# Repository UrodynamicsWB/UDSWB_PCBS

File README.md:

# UDSWB_PCBS

Several PCBs are required in order to manufacture the low-cost urodynamics system. The required file shave been supplied in thi repository.
The system requires one System Controller PCB and two Pressure Sensor PCBs to perform an investigtion.
When manufacturing the system it is best to order 5 System Controller PCBs and 10 Pressure Sensor PCBs (more if there is likely to be a high volume of investigations).

Below are the steps required to order the PCBS.

1. Send the "System Controller PCB\SYSCONTR PCB Gerber" directory to a zipped folder
2. Uploade the zipped folder to a PCB manufacture of your choice (Nb. Check the gerber file using an online viewer, often found on the manufactures website)
3. Place an order for the PCB
4. Repeat these steps for the pressure sensor pcb using the "Pressure Sensor PCB\PSENS PCB Gerber" directory

The KiCad files used to design the PCBs can be found in the "System Controller PCB\KiCad Files" and "Pressure Sensor PCB\KiCad Files" directories.

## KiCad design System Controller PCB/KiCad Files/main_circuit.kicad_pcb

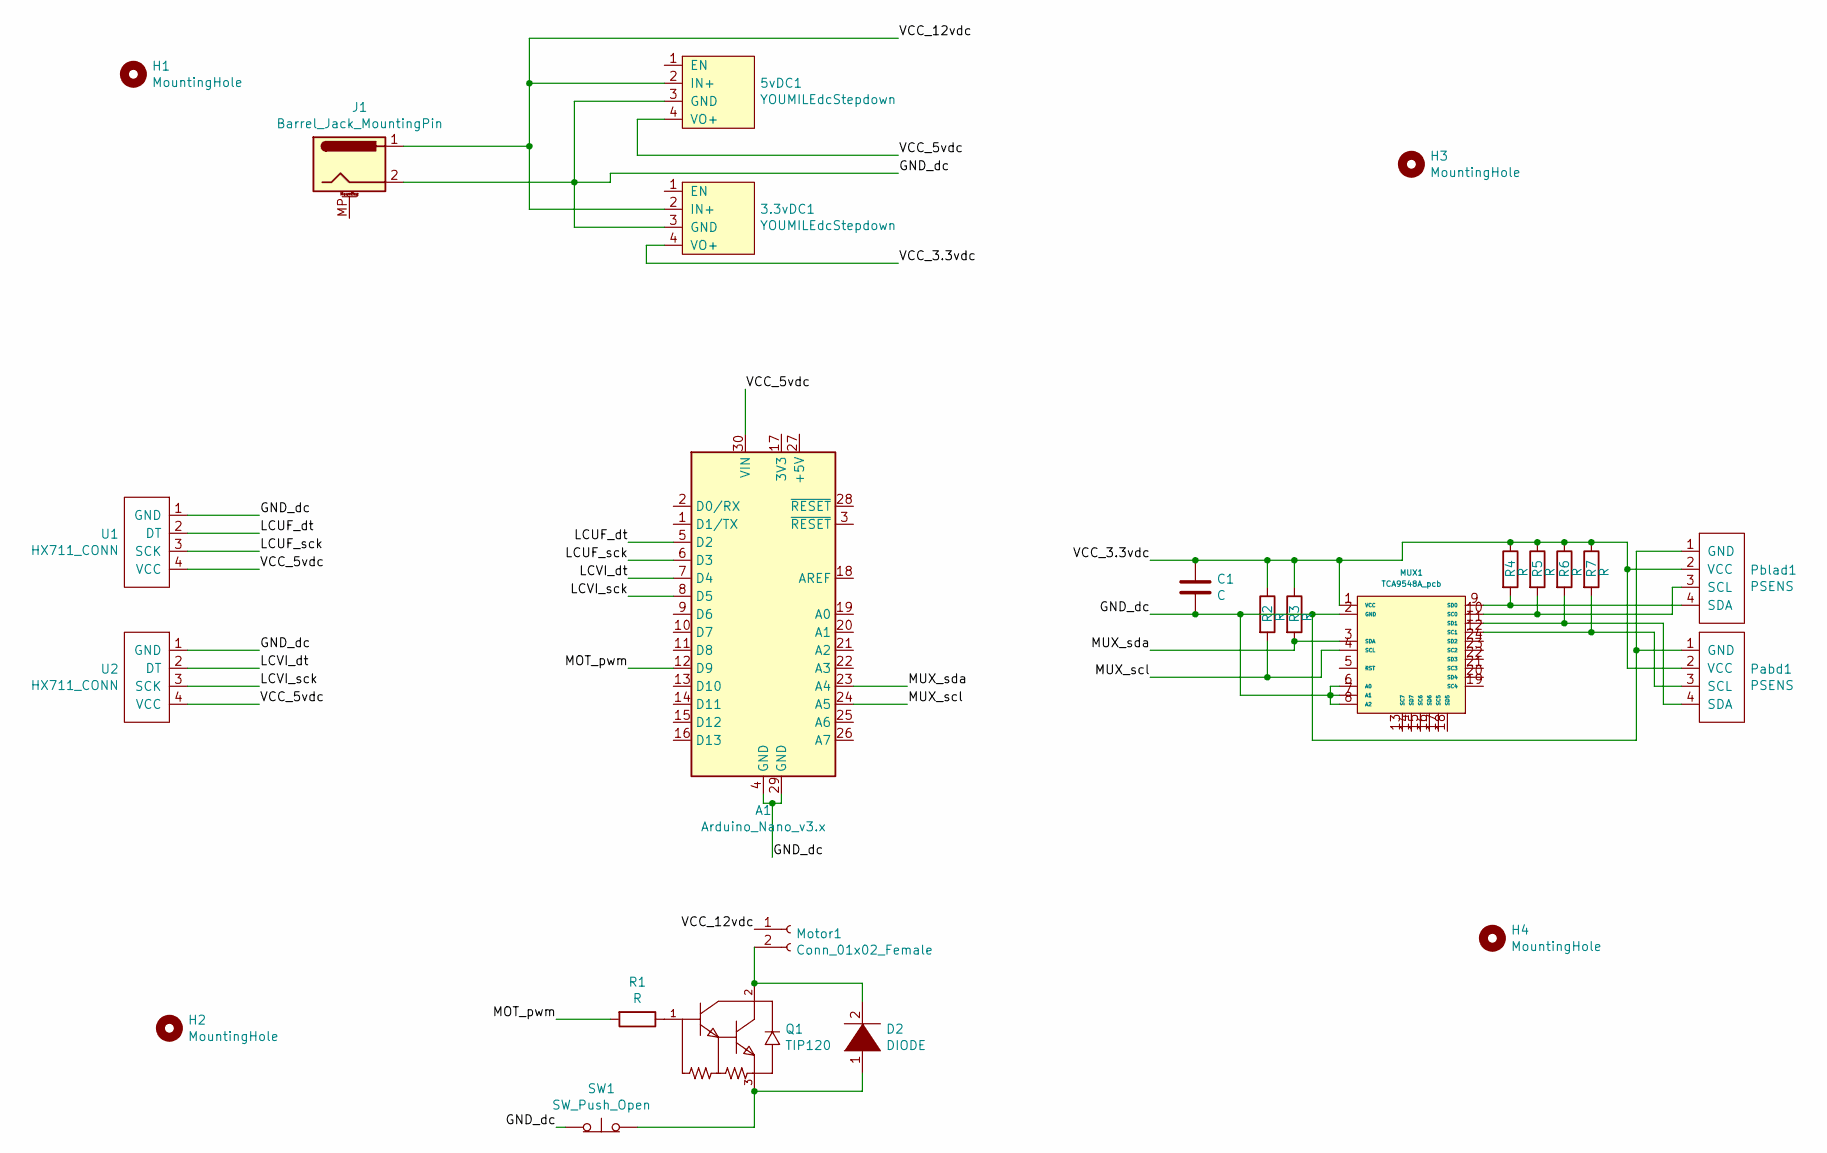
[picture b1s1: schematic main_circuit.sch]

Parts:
3.3vDC1, 5vDC1: YOUMILEdcStepdown
A1: Arduino_Nano_v3.x; Arduino_Nano
C1: C; CP_Radial_D6.3mm_P2.50mm
D2: DIODE; D_5KP_P10.16mm_Horizontal
H1, H2, H3, H4: MountingHole; MountingHole_6.4mm_M6
J1: Barrel_Jack_MountingPin; BarrelJack_Horizontal
MUX1: TCA9548A_pcb
Motor1: Conn_01x02_Female; PinHeader_1x02_P2.54mm_Vertical
Pabd1: PSENS
Pblad1: PSENS
Q1: TIP120; PinHeader_1x03_P2.54mm_Vertical
R1, R2, R3, R4, R5, R6, R7: R; R_Axial_DIN0207_L6.3mm_D2.5mm_P7.62mm_Horizontal
SW1: SW_Push_Open; PinSocket_1x02_P2.54mm_Vertical
U1, U2: HX711_CONN

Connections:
/GND_dc: 3.3vDC1.3 (GND), 5vDC1.3 (GND), A1.4 (GND), A1.29 (GND), C1.2, J1.2, MUX1.2 (GND), MUX1.6 (A0), MUX1.7 (A1), MUX1.8 (A2), Pabd1.1 (GND), Pblad1.1 (GND), SW1.1 (A), U1.1 (GND), U2.1 (GND)
/LCUF_dt: A1.5 (D2), U1.2 (DT)
/LCUF_sck: A1.6 (D3), U1.3 (SCK)
/LCVI_dt: A1.7 (D4), U2.2 (DT)
/LCVI_sck: A1.8 (D5), U2.3 (SCK)
/MOT_pwm: A1.12 (D9), R1.2
/MUX_scl: A1.24 (A5), MUX1.4 (SCL), R2.2
/MUX_sda: A1.23 (A4), MUX1.3 (SDA), R3.2
/VCC_3.3vdc: 3.3vDC1.4 (VO+), C1.1, MUX1.1 (VCC), Pabd1.2 (VCC), Pblad1.2 (VCC), R2.1, R3.1, R4.1, R5.1, R6.1, R7.1
/VCC_5vdc: 5vDC1.4 (VO+), A1.30 (VIN), U1.4 (VCC), U2.4 (VCC)
/VCC_12vdc: 3.3vDC1.2 (IN+), 5vDC1.2 (IN+), J1.1, Motor1.1
unnamed: D2.1 (K), Q1.3 (E), SW1.2 (B)
unnamed: D2.2 (A), Motor1.2, Q1.2 (C)
unnamed: MUX1.9 (SD0), Pblad1.4 (SDA), R4.2
unnamed: MUX1.10 (SC0), Pblad1.3 (SCL), R5.2
unnamed: MUX1.11 (SD1), Pabd1.4 (SDA), R6.2
unnamed: MUX1.12 (SC1), Pabd1.3 (SCL), R7.2
unnamed: Q1.1 (B), R1.1

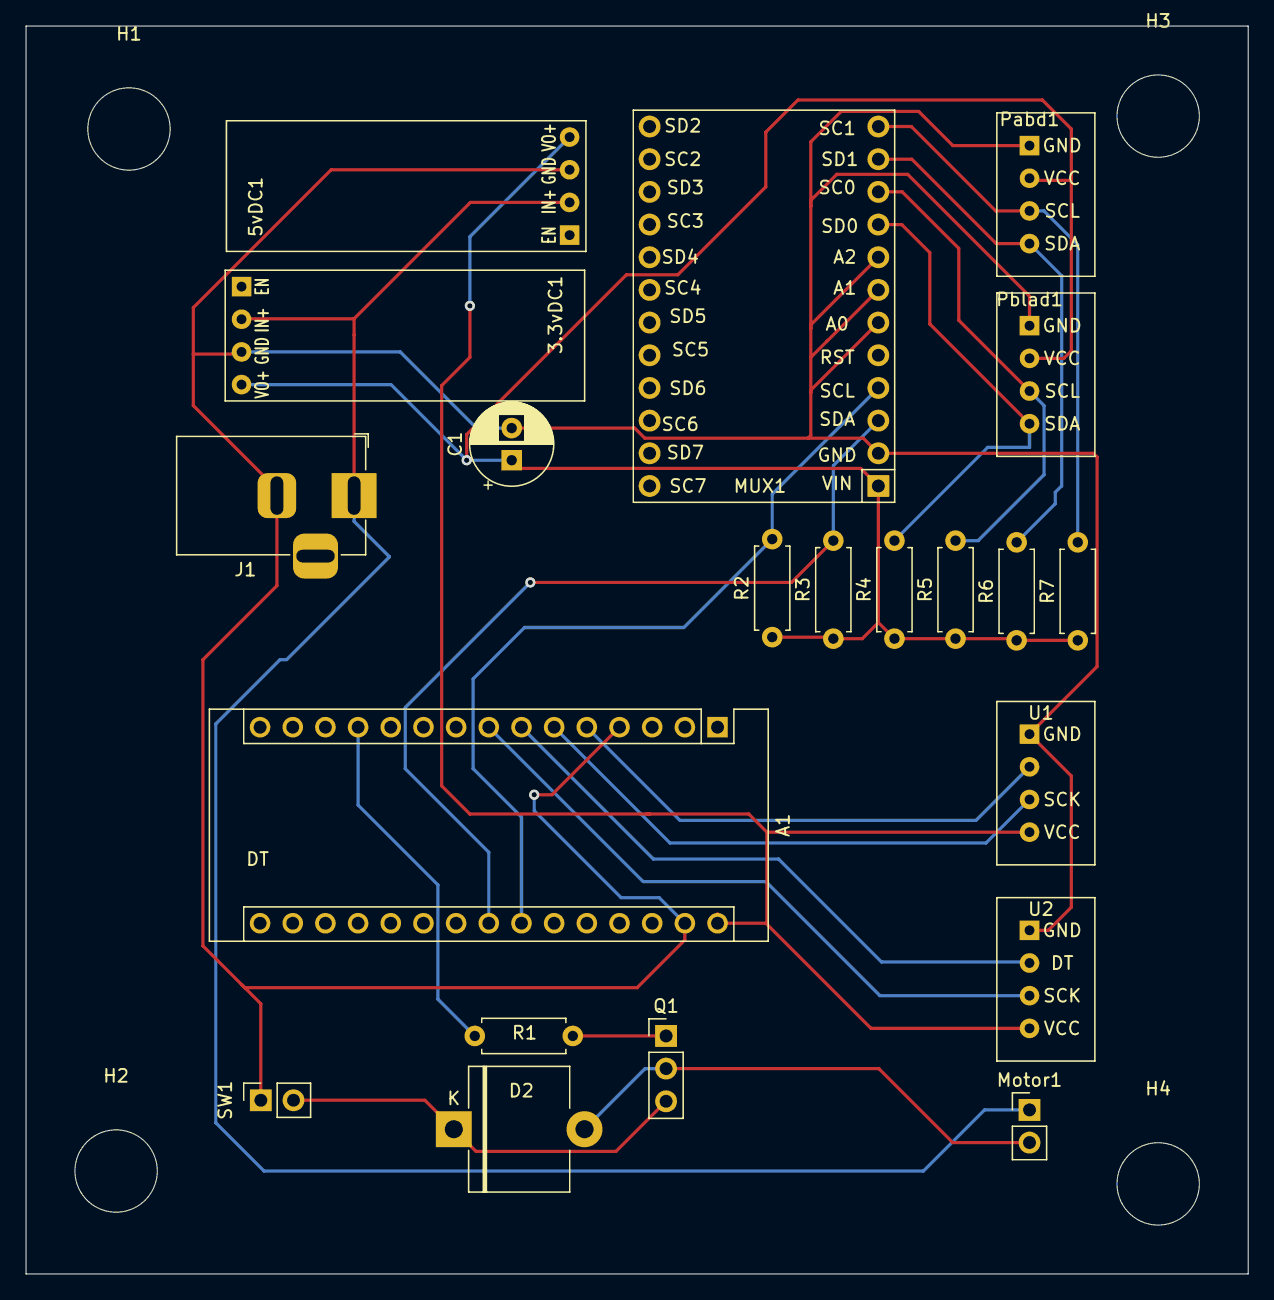
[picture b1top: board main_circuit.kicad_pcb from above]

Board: 2 copper layers, 95.0 x 97.0 mm, 25 parts (0 on the bottom side), 18 nets.

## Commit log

2022-11-11 Added all PCB files to repo
    System controller pcb files added
    Pressure sensor pcb files added
2022-11-11 Added readme
    Added pcb instructions
